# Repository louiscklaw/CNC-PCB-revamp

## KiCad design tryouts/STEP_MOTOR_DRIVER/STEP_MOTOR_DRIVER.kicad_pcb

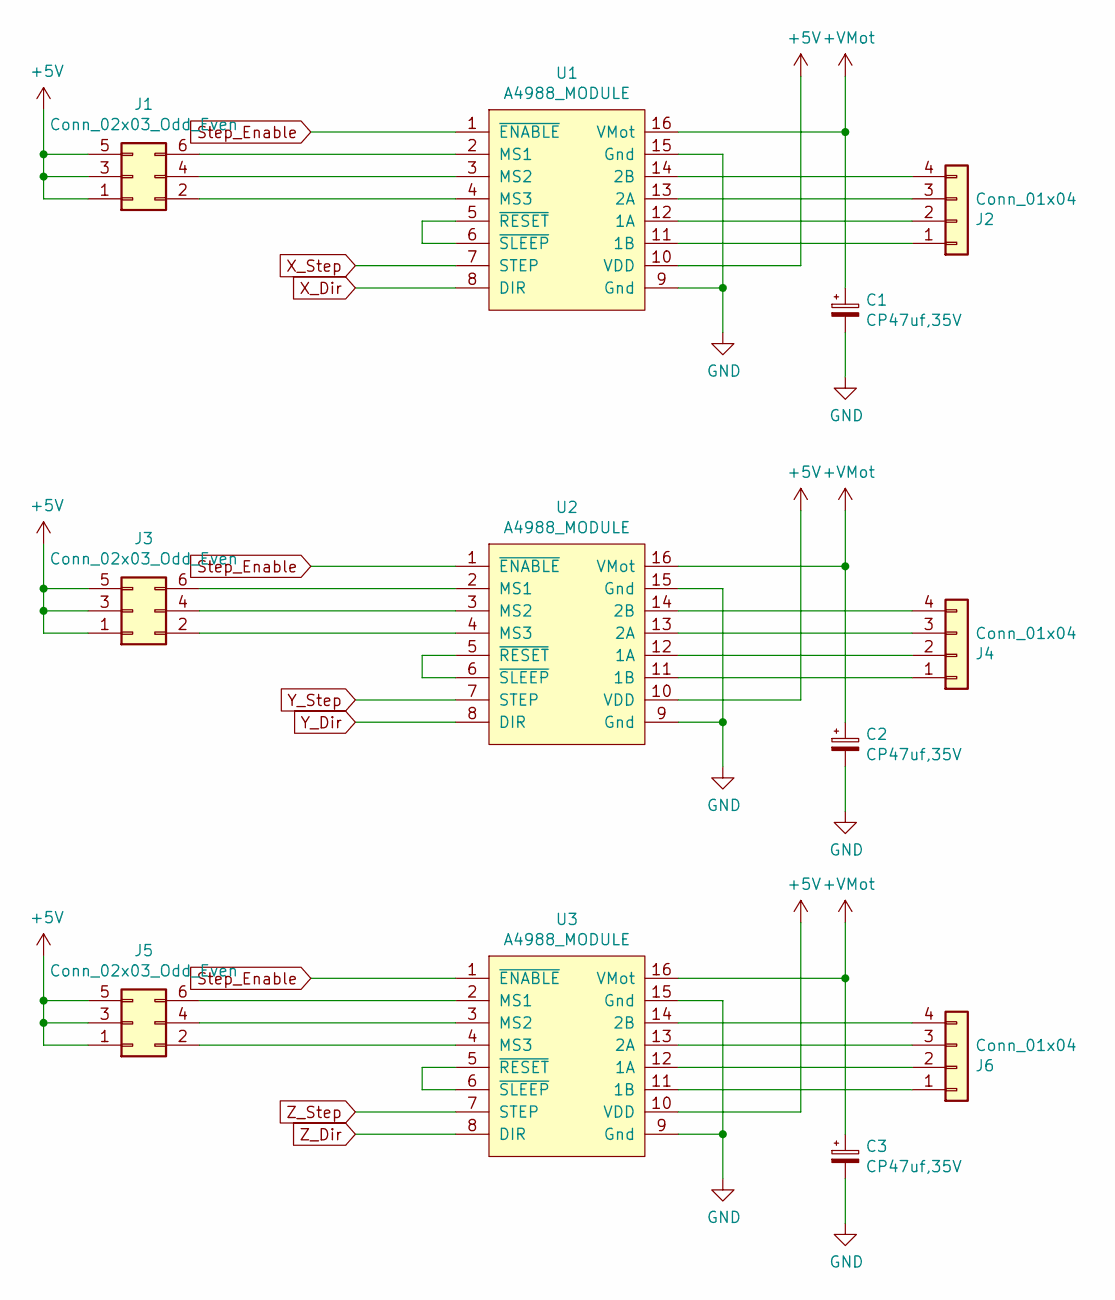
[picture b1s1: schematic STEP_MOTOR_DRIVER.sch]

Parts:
C1, C2, C3: CP47uf,35V; c_elec_5x5.3
J1, J3, J5: Conn_02x03_Odd_Even; PinHeader_2x03_P2.54mm_Vertical
J2, J4, J6: Conn_01x04; JST_XH_S04B-XH-A-1_1x04_P2.50mm_Horizontal
U1, U2, U3: A4988_MODULE; Pololu_Breakout-16_15.2x20.3mm

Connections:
+5V: J1.1, J1.3, J1.5, J3.1, J3.3, J3.5, J5.1, J5.3, J5.5, U1.10 (VDD), U2.10 (VDD), U3.10 (VDD)
+VMot: C1.1, C2.1, C3.1, U1.16 (VMot), U2.16 (VMot), U3.16 (VMot)
GND: C1.2, C2.2, C3.2, U1.9 (Gnd), U1.15 (Gnd), U2.9 (Gnd), U2.15 (Gnd), U3.9 (Gnd), U3.15 (Gnd)
unnamed: J1.2, U1.4 (MS3)
unnamed: J1.4, U1.3 (MS2)
unnamed: J1.6, U1.2 (MS1)
unnamed: J2.1, U1.11 (1B)
unnamed: J2.2, U1.12 (1A)
unnamed: J2.3, U1.13 (2A)
unnamed: J2.4, U1.14 (2B)
unnamed: J3.2, U2.4 (MS3)
unnamed: J3.4, U2.3 (MS2)
unnamed: J3.6, U2.2 (MS1)
unnamed: J4.1, U2.11 (1B)
unnamed: J4.2, U2.12 (1A)
unnamed: J4.3, U2.13 (2A)
unnamed: J4.4, U2.14 (2B)
unnamed: J5.2, U3.4 (MS3)
unnamed: J5.4, U3.3 (MS2)
unnamed: J5.6, U3.2 (MS1)
unnamed: J6.1, U3.11 (1B)
unnamed: J6.2, U3.12 (1A)
unnamed: J6.3, U3.13 (2A)
unnamed: J6.4, U3.14 (2B)
unnamed: U1.5 (~RESET~), U1.6 (~SLEEP~)
unnamed: U2.5 (~RESET~), U2.6 (~SLEEP~)
unnamed: U3.5 (~RESET~), U3.6 (~SLEEP~)
Step_Enable: U1.1 (~ENABLE~), U2.1 (~ENABLE~), U3.1 (~ENABLE~)
X_Dir: U1.8 (DIR)
X_Step: U1.7 (STEP)
Y_Dir: U2.8 (DIR)
Y_Step: U2.7 (STEP)
Z_Dir: U3.8 (DIR)
Z_Step: U3.7 (STEP)

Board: 2 copper layers, 12 parts (0 on the bottom side), 28 nets, no tracks yet.

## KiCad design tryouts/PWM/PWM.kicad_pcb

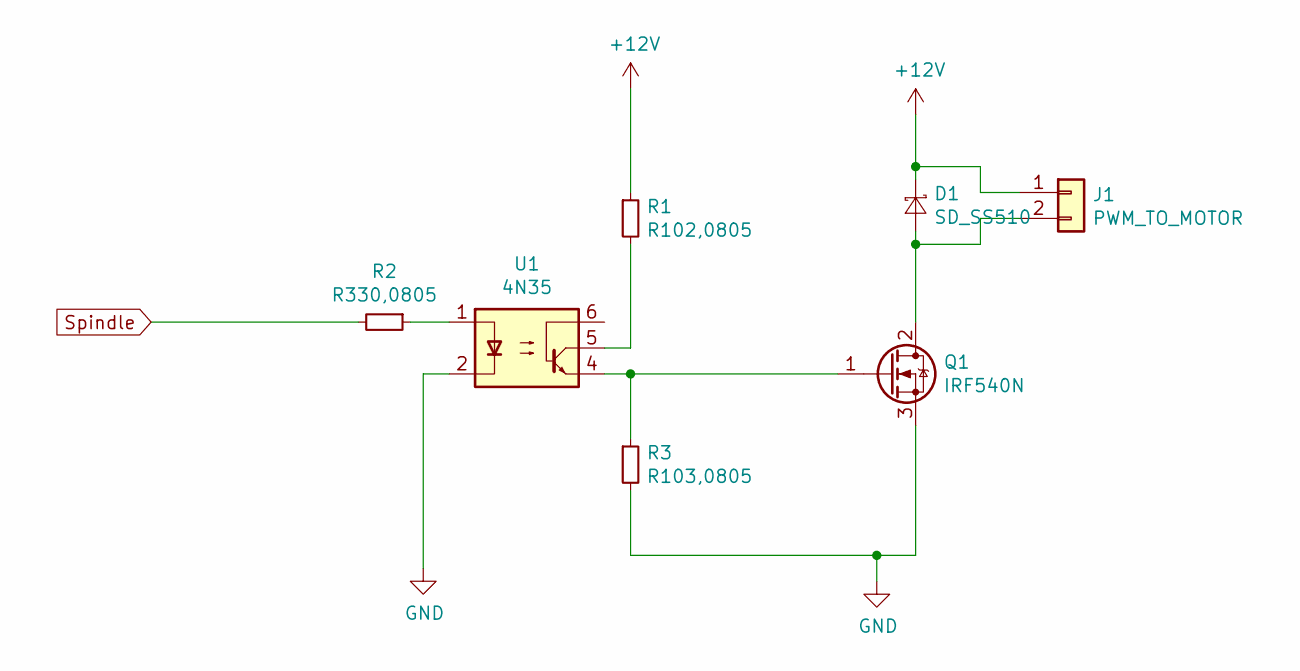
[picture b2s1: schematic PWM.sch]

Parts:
D1: SD_SS510; D_1206_3216Metric_Pad1.42x1.75mm_HandSolder
J1: PWM_TO_MOTOR; PinHeader_1x02_P2.54mm_Vertical
Q1: IRF540N; TO-263-2
R1: R102,0805; R_0805_2012Metric_Pad1.15x1.40mm_HandSolder
R2: R330,0805; R_0805_2012Metric_Pad1.15x1.40mm_HandSolder
R3: R103,0805; R_0805_2012Metric_Pad1.15x1.40mm_HandSolder
U1: 4N35; DIP-6_W7.62mm

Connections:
+12V: D1.1 (K), J1.1, R1.1
GND: Q1.3 (S), R3.2, U1.2
unnamed: D1.2 (A), J1.2, Q1.2 (D)
unnamed: Q1.1 (G), R3.1, U1.4
unnamed: R1.2, U1.5
unnamed: R2.1, U1.1
Spindle: R2.2

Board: 2 copper layers, 7 parts (0 on the bottom side), 6 nets, no tracks yet.

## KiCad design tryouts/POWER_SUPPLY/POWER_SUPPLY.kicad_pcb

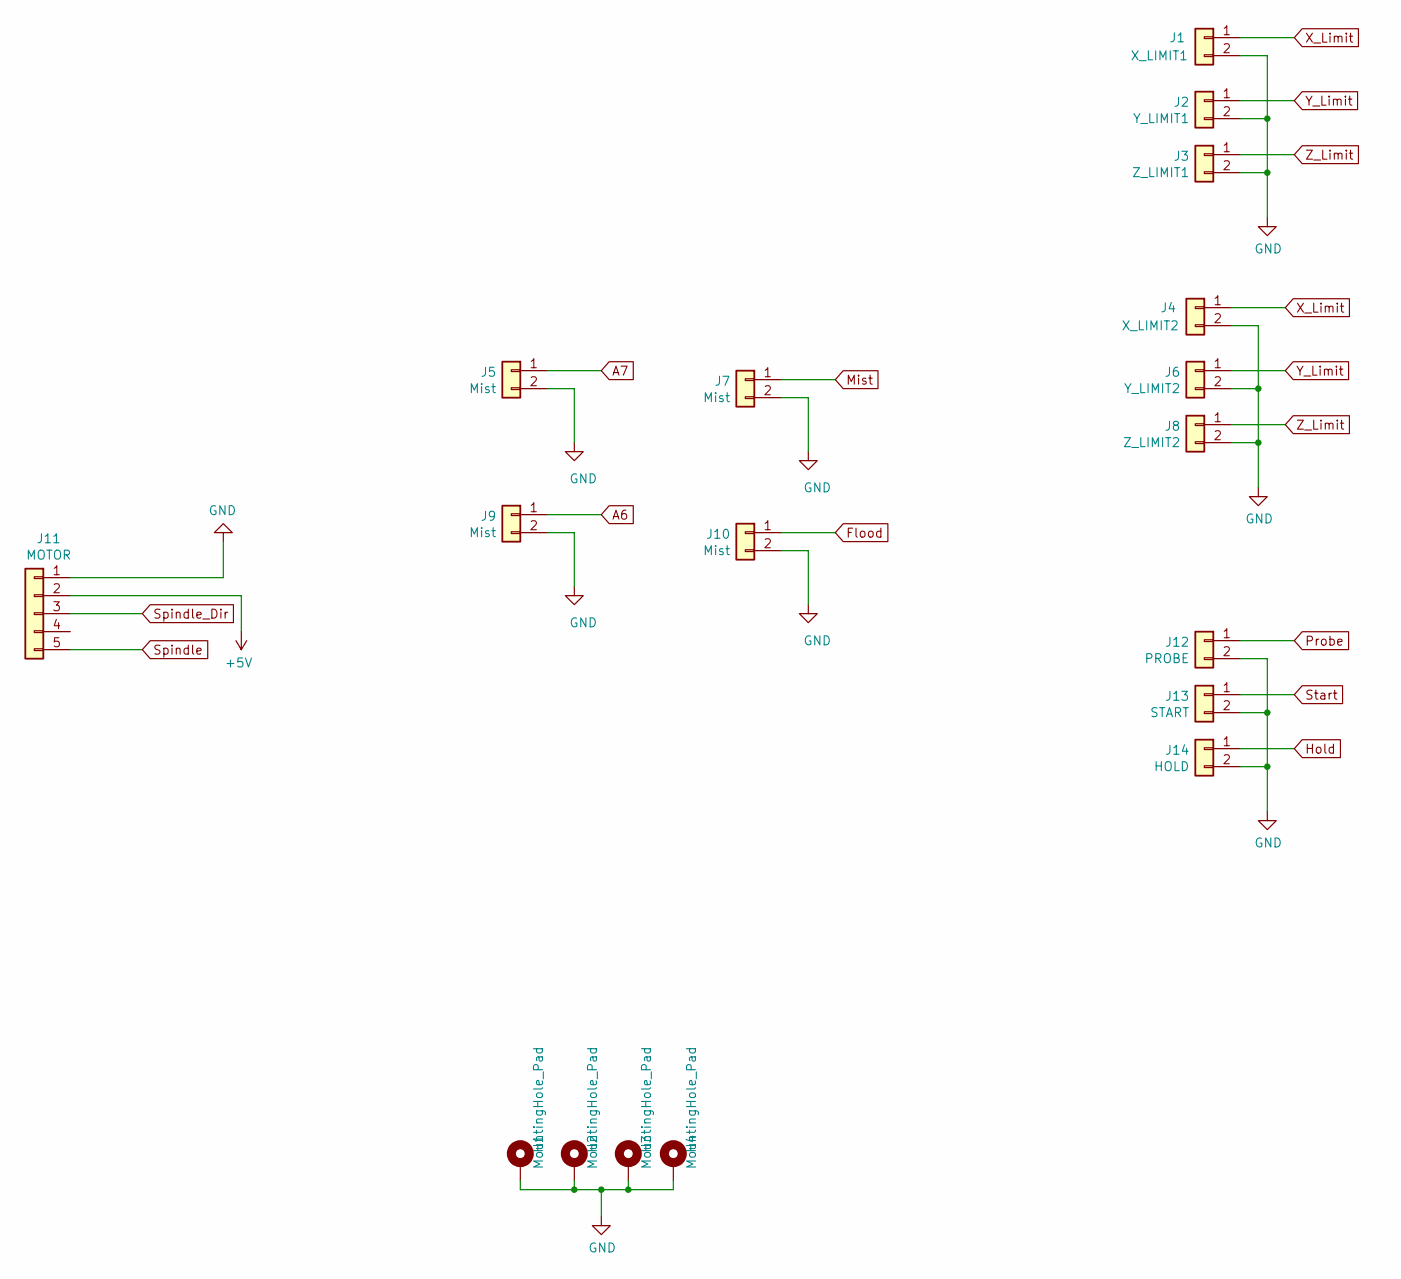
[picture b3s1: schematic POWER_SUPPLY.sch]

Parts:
H1, H2, H3, H4: MountingHole_Pad; MountingHole_2.7mm_M2.5_Pad
J1: X_LIMIT1; JST_XH_S02B-XH-A-1_1x02_P2.50mm_Horizontal
J2: Y_LIMIT1; JST_XH_S02B-XH-A-1_1x02_P2.50mm_Horizontal
J3: Z_LIMIT1; JST_XH_S02B-XH-A-1_1x02_P2.50mm_Horizontal
J4: X_LIMIT2; JST_XH_S02B-XH-A-1_1x02_P2.50mm_Horizontal
J5, J7, J9, J10: Mist; JST_XH_S02B-XH-A-1_1x02_P2.50mm_Horizontal
J6: Y_LIMIT2; JST_XH_S02B-XH-A-1_1x02_P2.50mm_Horizontal
J8: Z_LIMIT2; JST_XH_S02B-XH-A-1_1x02_P2.50mm_Horizontal
J11: MOTOR; JST_XH_S05B-XH-A-1_1x05_P2.50mm_Horizontal
J12: PROBE; JST_XH_S02B-XH-A-1_1x02_P2.50mm_Horizontal
J13: START; JST_XH_S02B-XH-A-1_1x02_P2.50mm_Horizontal
J14: HOLD; JST_XH_S02B-XH-A-1_1x02_P2.50mm_Horizontal

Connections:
+5V: J11.2
A6: J9.1
A7: J5.1
Flood: J10.1
GND: H1.1, H2.1, H3.1, H4.1, J1.2, J2.2, J3.2, J4.2, J5.2, J6.2, J7.2, J8.2, J9.2, J10.2, J11.1, J12.2, J13.2, J14.2
Hold: J14.1
Mist: J7.1
Probe: J12.1
Spindle: J11.5
Spindle_Dir: J11.3
Start: J13.1
X_Limit: J1.1, J4.1
Y_Limit: J2.1, J6.1
Z_Limit: J3.1, J8.1

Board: 2 copper layers, 18 parts (0 on the bottom side), 4 nets, no tracks yet.

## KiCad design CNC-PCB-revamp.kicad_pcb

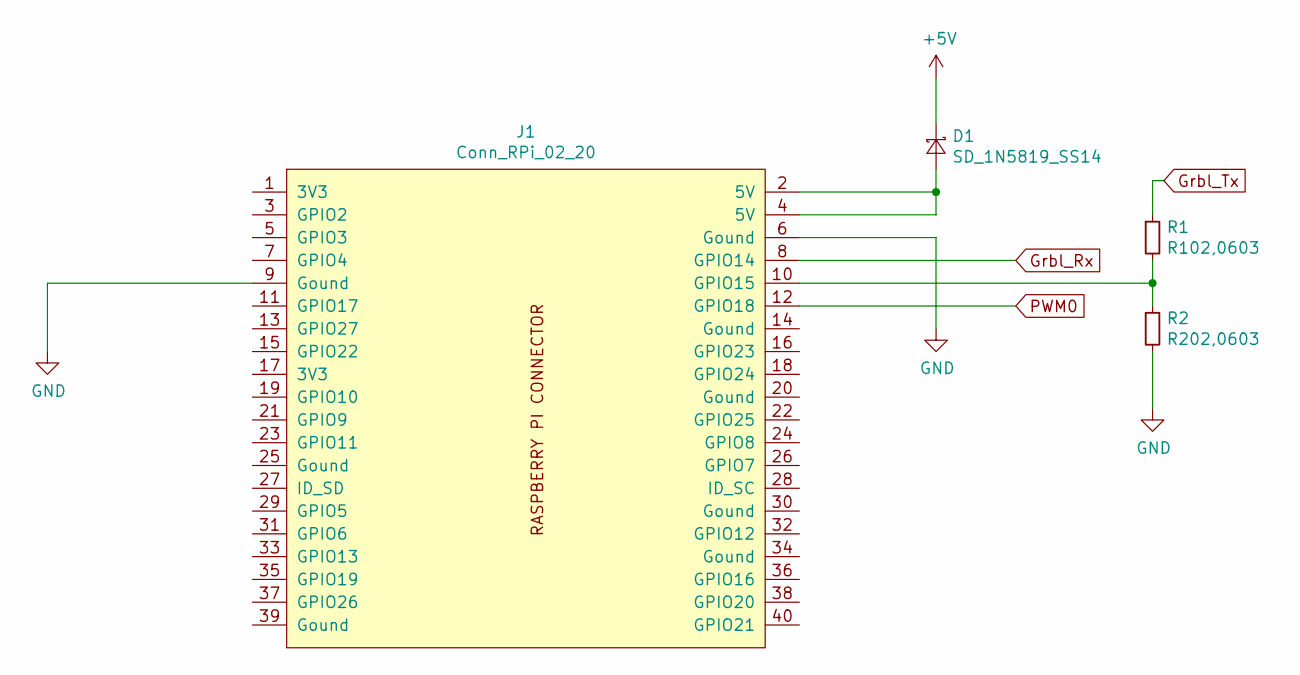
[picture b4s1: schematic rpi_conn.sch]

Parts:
D1: SD_1N5819_SS14; D_1206_3216Metric_Pad1.42x1.75mm_HandSolder
J1: Conn_RPi_02_20
R1: R102,0603; R_0603_1608Metric_Pad1.05x0.95mm_HandSolder
R2: R202,0603; R_0603_1608Metric_Pad1.05x0.95mm_HandSolder

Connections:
+5V: D1.1 (K); also elsewhere on the board
GND: J1.6 (Gound), J1.9 (Gound), R2.2; also elsewhere on the board
Grbl_Rx: J1.8 (GPIO14); also elsewhere on the board
Grbl_Tx: R1.1; also elsewhere on the board
unnamed: D1.2 (A), J1.2 (5V), J1.4 (5V)
unnamed: J1.10 (GPIO15), R1.2, R2.1
PWM0: J1.12 (GPIO18)

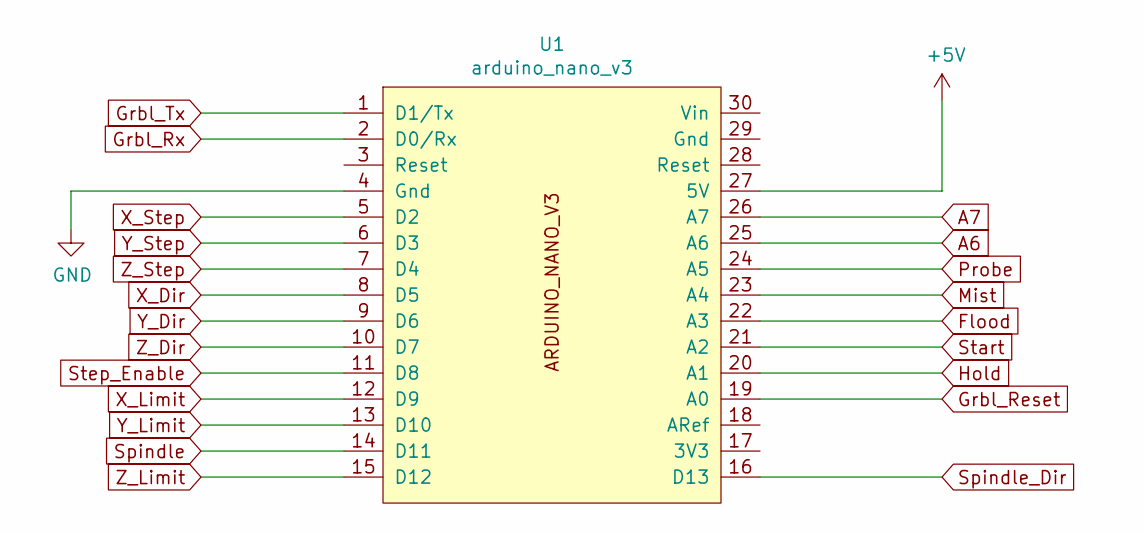
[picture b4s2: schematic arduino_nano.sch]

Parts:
U1: arduino_nano_v3; Arduino_Nano

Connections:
+5V: U1.27 (5V); also elsewhere on the board
A6: U1.25 (A6); also elsewhere on the board
A7: U1.26 (A7); also elsewhere on the board
Flood: U1.22 (A3); also elsewhere on the board
GND: U1.4 (Gnd); also elsewhere on the board
Grbl_Reset: U1.19 (A0)
Grbl_Rx: U1.2 (D0/Rx); also elsewhere on the board
Grbl_Tx: U1.1 (D1/Tx); also elsewhere on the board
Hold: U1.20 (A1); also elsewhere on the board
Mist: U1.23 (A4); also elsewhere on the board
Probe: U1.24 (A5); also elsewhere on the board
Spindle: U1.14 (D11); also elsewhere on the board
Spindle_Dir: U1.16 (D13); also elsewhere on the board
Start: U1.21 (A2); also elsewhere on the board
Step_Enable: U1.11 (D8); also elsewhere on the board
X_Dir: U1.8 (D5); also elsewhere on the board
X_Limit: U1.12 (D9); also elsewhere on the board
X_Step: U1.5 (D2); also elsewhere on the board
Y_Dir: U1.9 (D6); also elsewhere on the board
Y_Limit: U1.13 (D10); also elsewhere on the board
Y_Step: U1.6 (D3); also elsewhere on the board
Z_Dir: U1.10 (D7); also elsewhere on the board
Z_Limit: U1.15 (D12); also elsewhere on the board
Z_Step: U1.7 (D4); also elsewhere on the board

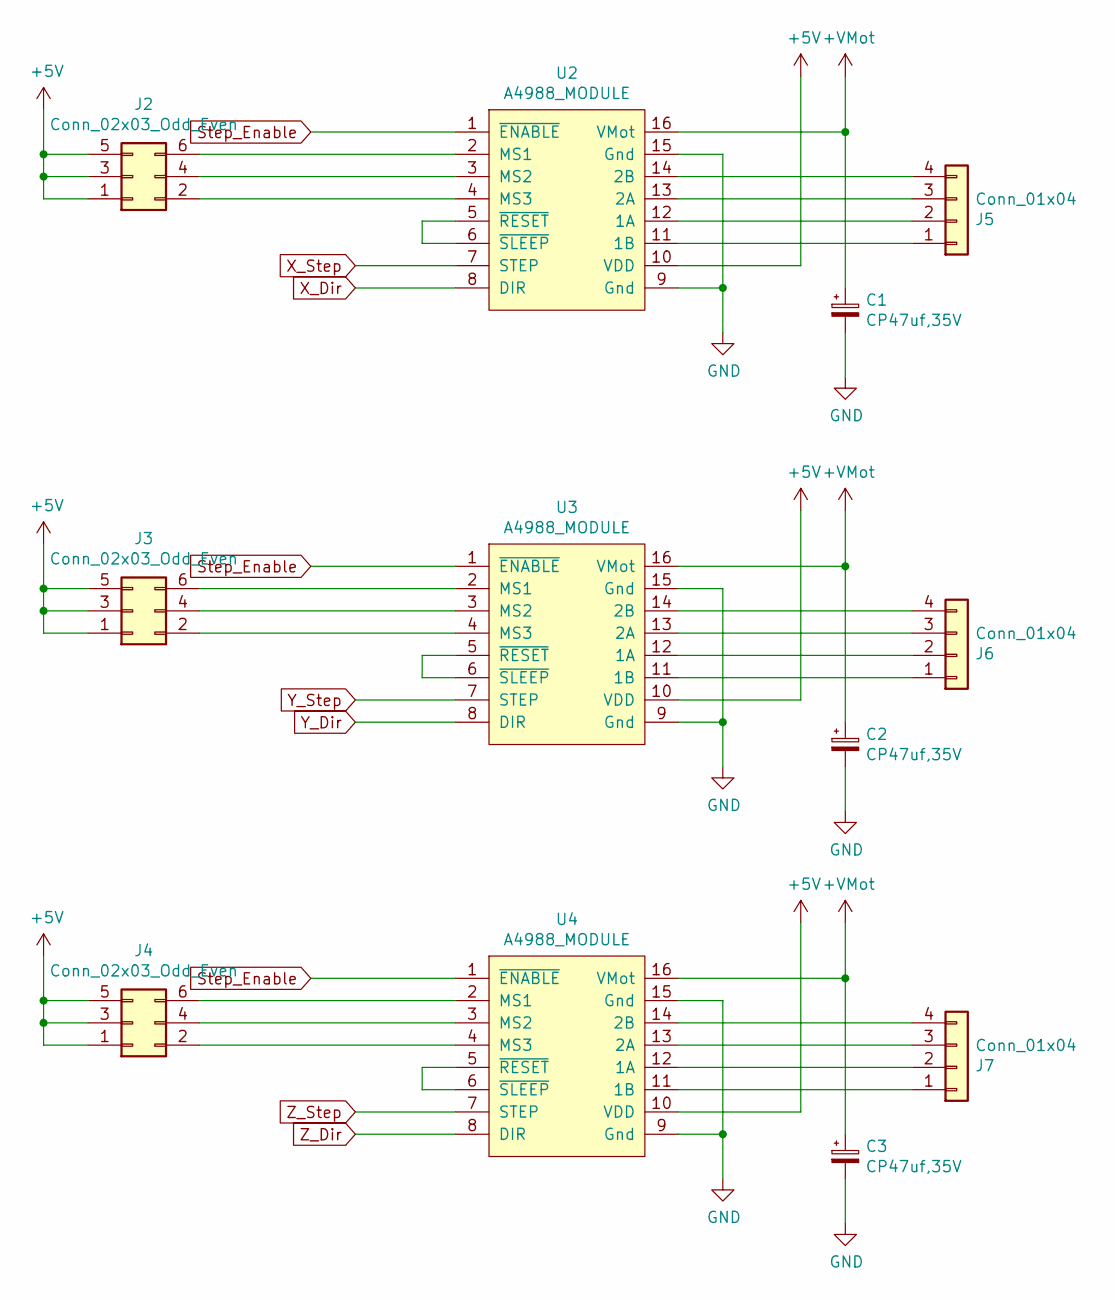
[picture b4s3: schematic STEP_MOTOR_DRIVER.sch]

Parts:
C1, C2, C3: CP47uf,35V; c_elec_5x5.3
J2, J3, J4: Conn_02x03_Odd_Even; PinHeader_2x03_P2.54mm_Vertical
J5, J6, J7: Conn_01x04; JST_XH_S04B-XH-A-1_1x04_P2.50mm_Horizontal
U2, U3, U4: A4988_MODULE; Pololu_Breakout-16_15.2x20.3mm

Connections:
+5V: J2.1, J2.3, J2.5, J3.1, J3.3, J3.5, J4.1, J4.3, J4.5, U2.10 (VDD), U3.10 (VDD), U4.10 (VDD); also elsewhere on the board
+VMot: C1.1, C2.1, C3.1, U2.16 (VMot), U3.16 (VMot), U4.16 (VMot)
GND: C1.2, C2.2, C3.2, U2.9 (Gnd), U2.15 (Gnd), U3.9 (Gnd), U3.15 (Gnd), U4.9 (Gnd), U4.15 (Gnd); also elsewhere on the board
unnamed: J2.2, U2.4 (MS3)
unnamed: J2.4, U2.3 (MS2)
unnamed: J2.6, U2.2 (MS1)
unnamed: J3.2, U3.4 (MS3)
unnamed: J3.4, U3.3 (MS2)
unnamed: J3.6, U3.2 (MS1)
unnamed: J4.2, U4.4 (MS3)
unnamed: J4.4, U4.3 (MS2)
unnamed: J4.6, U4.2 (MS1)
unnamed: J5.1, U2.11 (1B)
unnamed: J5.2, U2.12 (1A)
unnamed: J5.3, U2.13 (2A)
unnamed: J5.4, U2.14 (2B)
unnamed: J6.1, U3.11 (1B)
unnamed: J6.2, U3.12 (1A)
unnamed: J6.3, U3.13 (2A)
unnamed: J6.4, U3.14 (2B)
unnamed: J7.1, U4.11 (1B)
unnamed: J7.2, U4.12 (1A)
unnamed: J7.3, U4.13 (2A)
unnamed: J7.4, U4.14 (2B)
unnamed: U2.5 (~RESET~), U2.6 (~SLEEP~)
unnamed: U3.5 (~RESET~), U3.6 (~SLEEP~)
unnamed: U4.5 (~RESET~), U4.6 (~SLEEP~)
Step_Enable: U2.1 (~ENABLE~), U3.1 (~ENABLE~), U4.1 (~ENABLE~); also elsewhere on the board
X_Dir: U2.8 (DIR); also elsewhere on the board
X_Step: U2.7 (STEP); also elsewhere on the board
Y_Dir: U3.8 (DIR); also elsewhere on the board
Y_Step: U3.7 (STEP); also elsewhere on the board
Z_Dir: U4.8 (DIR); also elsewhere on the board
Z_Step: U4.7 (STEP); also elsewhere on the board

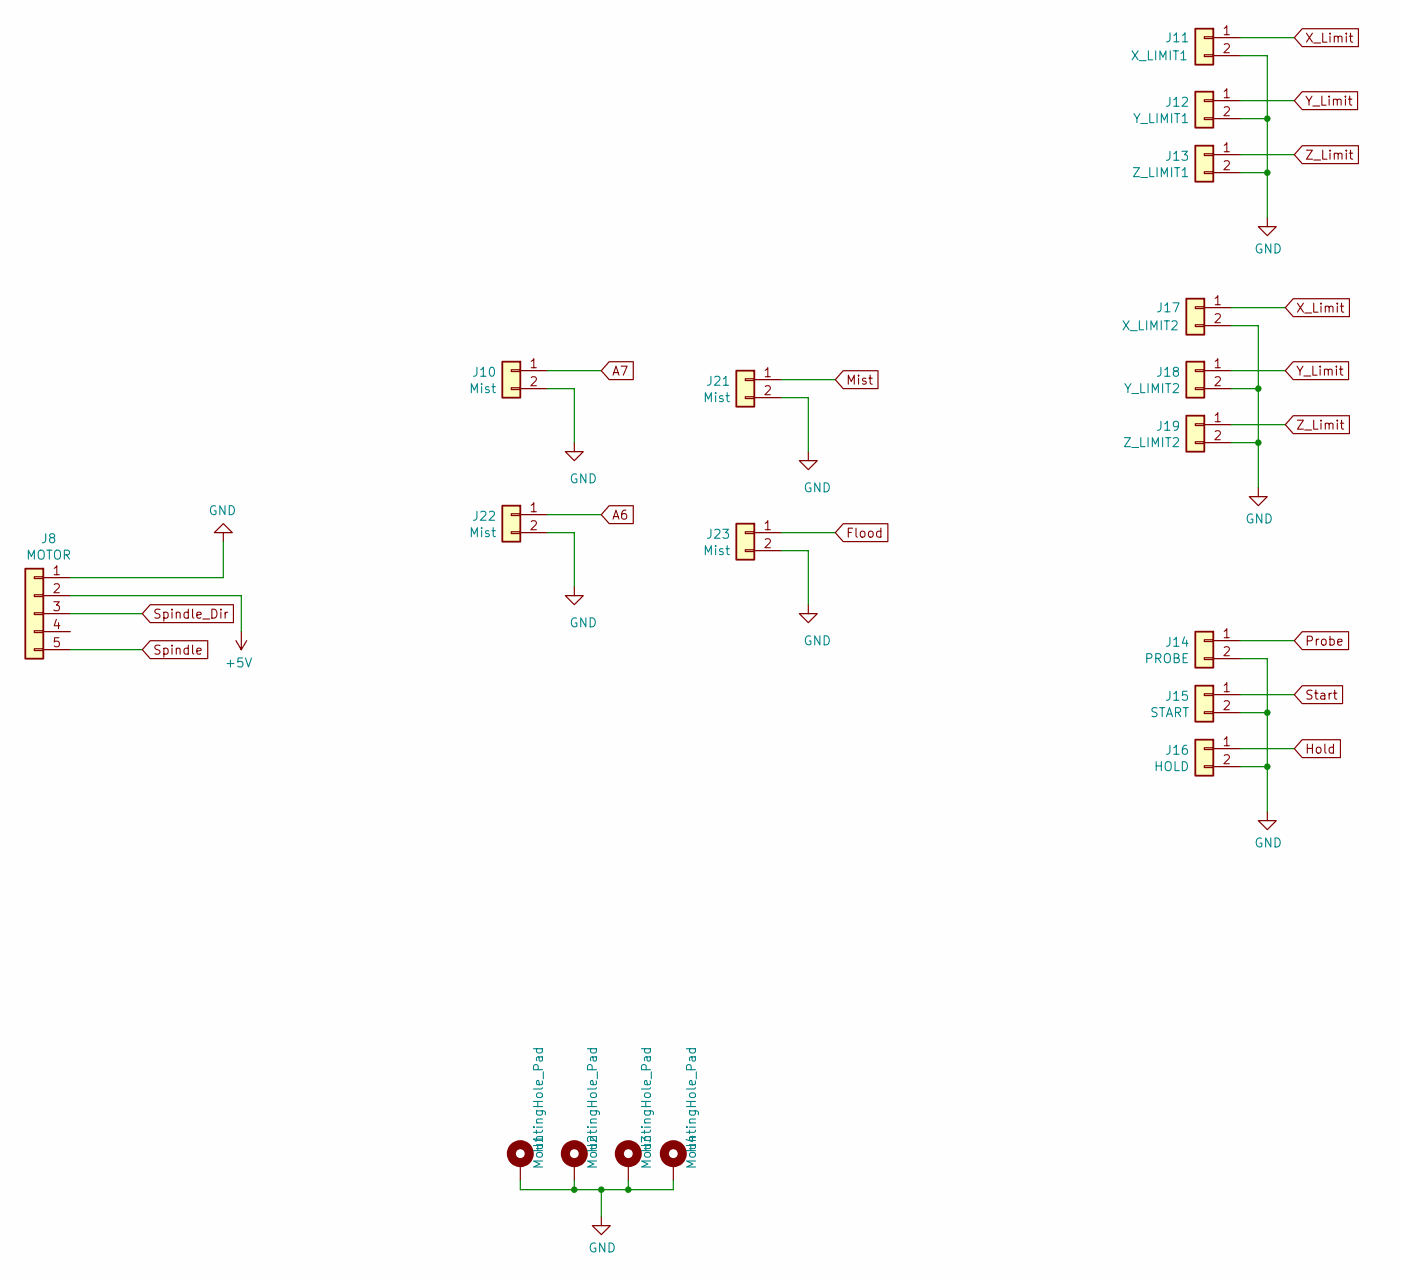
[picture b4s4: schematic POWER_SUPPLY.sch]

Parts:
H1, H2, H3, H4: MountingHole_Pad; MountingHole_2.7mm_M2.5_Pad
J8: MOTOR; JST_XH_S05B-XH-A-1_1x05_P2.50mm_Horizontal
J10, J21, J22, J23: Mist; JST_XH_S02B-XH-A-1_1x02_P2.50mm_Horizontal
J11: X_LIMIT1; JST_XH_S02B-XH-A-1_1x02_P2.50mm_Horizontal
J12: Y_LIMIT1; JST_XH_S02B-XH-A-1_1x02_P2.50mm_Horizontal
J13: Z_LIMIT1; JST_XH_S02B-XH-A-1_1x02_P2.50mm_Horizontal
J14: PROBE; JST_XH_S02B-XH-A-1_1x02_P2.50mm_Horizontal
J15: START; JST_XH_S02B-XH-A-1_1x02_P2.50mm_Horizontal
J16: HOLD; JST_XH_S02B-XH-A-1_1x02_P2.50mm_Horizontal
J17: X_LIMIT2; JST_XH_S02B-XH-A-1_1x02_P2.50mm_Horizontal
J18: Y_LIMIT2; JST_XH_S02B-XH-A-1_1x02_P2.50mm_Horizontal
J19: Z_LIMIT2; JST_XH_S02B-XH-A-1_1x02_P2.50mm_Horizontal

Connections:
+5V: J8.2; also elsewhere on the board
A6: J22.1; also elsewhere on the board
A7: J10.1; also elsewhere on the board
Flood: J23.1; also elsewhere on the board
GND: H1.1, H2.1, H3.1, H4.1, J8.1, J10.2, J11.2, J12.2, J13.2, J14.2, J15.2, J16.2, J17.2, J18.2, J19.2, J21.2, J22.2, J23.2; also elsewhere on the board
Hold: J16.1; also elsewhere on the board
Mist: J21.1; also elsewhere on the board
Probe: J14.1; also elsewhere on the board
Spindle: J8.5; also elsewhere on the board
Spindle_Dir: J8.3; also elsewhere on the board
Start: J15.1; also elsewhere on the board
X_Limit: J11.1, J17.1; also elsewhere on the board
Y_Limit: J12.1, J18.1; also elsewhere on the board
Z_Limit: J13.1, J19.1; also elsewhere on the board

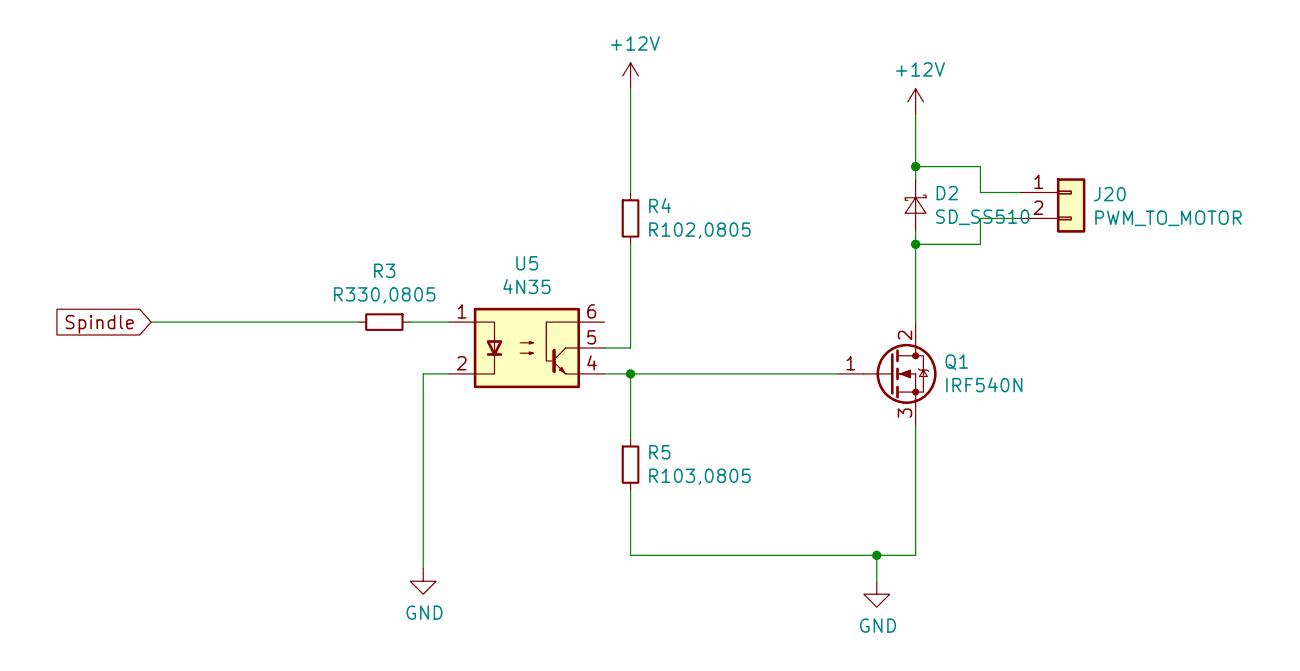
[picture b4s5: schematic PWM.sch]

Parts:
D2: SD_SS510; D_1206_3216Metric_Pad1.42x1.75mm_HandSolder
J20: PWM_TO_MOTOR; PinHeader_1x02_P2.54mm_Vertical
Q1: IRF540N; TO-263-2
R3: R330,0805; R_0805_2012Metric_Pad1.15x1.40mm_HandSolder
R4: R102,0805; R_0805_2012Metric_Pad1.15x1.40mm_HandSolder
R5: R103,0805; R_0805_2012Metric_Pad1.15x1.40mm_HandSolder
U5: 4N35; DIP-6_W7.62mm

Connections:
+12V: D2.1 (K), J20.1, R4.1; also elsewhere on the board
GND: Q1.3 (S), R5.2, U5.2; also elsewhere on the board
unnamed: D2.2 (A), J20.2, Q1.2 (D)
unnamed: Q1.1 (G), R5.1, U5.4
unnamed: R3.1, U5.1
unnamed: R4.2, U5.5
Spindle: R3.2; also elsewhere on the board

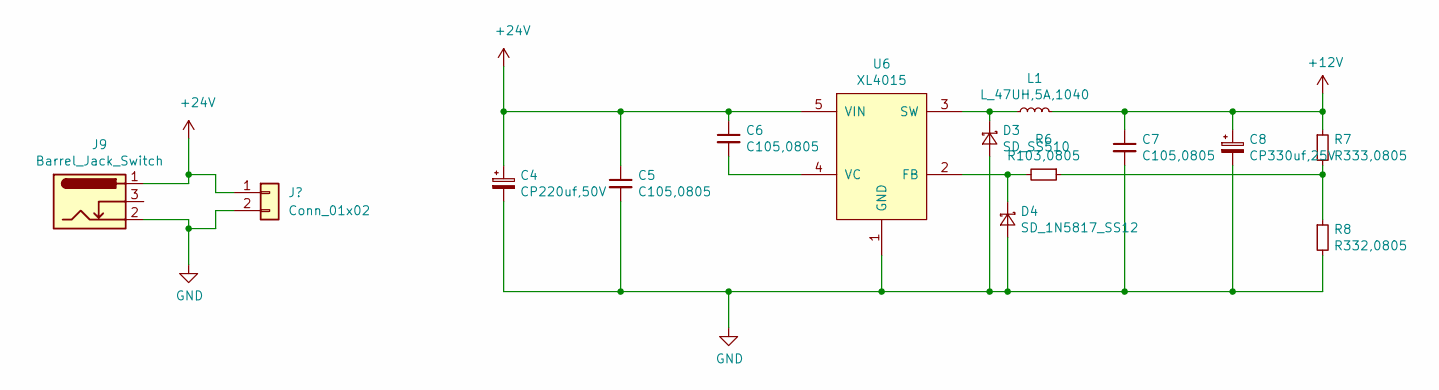
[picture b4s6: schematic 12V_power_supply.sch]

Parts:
C4: CP220uf,50V; CP_Elec_10x10.5
C5, C6, C7: C105,0805; C_0805_2012Metric_Pad1.15x1.40mm_HandSolder
C8: CP330uf,25V; CP_Elec_8x10.5
D3: SD_SS510; D_1206_3216Metric_Pad1.42x1.75mm_HandSolder
D4: SD_1N5817_SS12; D_1206_3216Metric_Pad1.42x1.75mm_HandSolder
J9: Barrel_Jack_Switch; BarrelJack_Horizontal
L1: L_47UH,5A,1040; L_Wuerth_HCI-1040
R6: R103,0805; R_0805_2012Metric_Pad1.15x1.40mm_HandSolder
R7: R333,0805; R_0805_2012Metric_Pad1.15x1.40mm_HandSolder
R8: R332,0805; R_0805_2012Metric_Pad1.15x1.40mm_HandSolder
U6: XL4015; TO-263-5_TabPin3

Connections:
+12V: C7.1, C8.1, L1.2, R7.1; also elsewhere on the board
+24V: C4.1, C5.1, C6.1, J9.1, U6.5 (VIN)
GND: C4.2, C5.2, C7.2, C8.2, D3.2 (A), D4.2 (A), J9.2, R8.2, U6.1 (GND); also elsewhere on the board
unnamed: C6.2, U6.4 (VC)
unnamed: D3.1 (K), L1.1, U6.3 (SW)
unnamed: D4.1 (K), R6.2, U6.2 (FB)
unnamed: R6.1, R7.2, R8.1

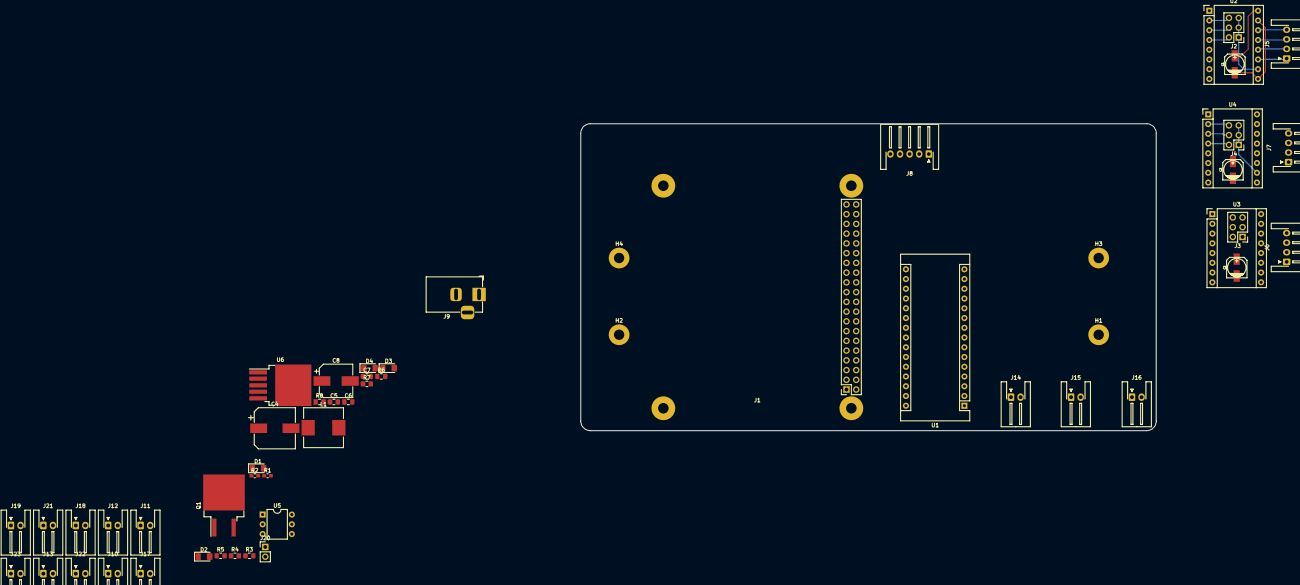
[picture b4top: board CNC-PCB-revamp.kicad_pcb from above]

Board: 2 copper layers, 150.0 x 80.0 mm, 55 parts (0 on the bottom side), 60 nets.

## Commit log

2018-11-26 upadte,
2018-11-26 update,
2018-11-26 remove bak files,
2018-11-26 update to delete bak,
2020-05-05 ci: init travis build config,
2020-05-05 ci: init travis token,
